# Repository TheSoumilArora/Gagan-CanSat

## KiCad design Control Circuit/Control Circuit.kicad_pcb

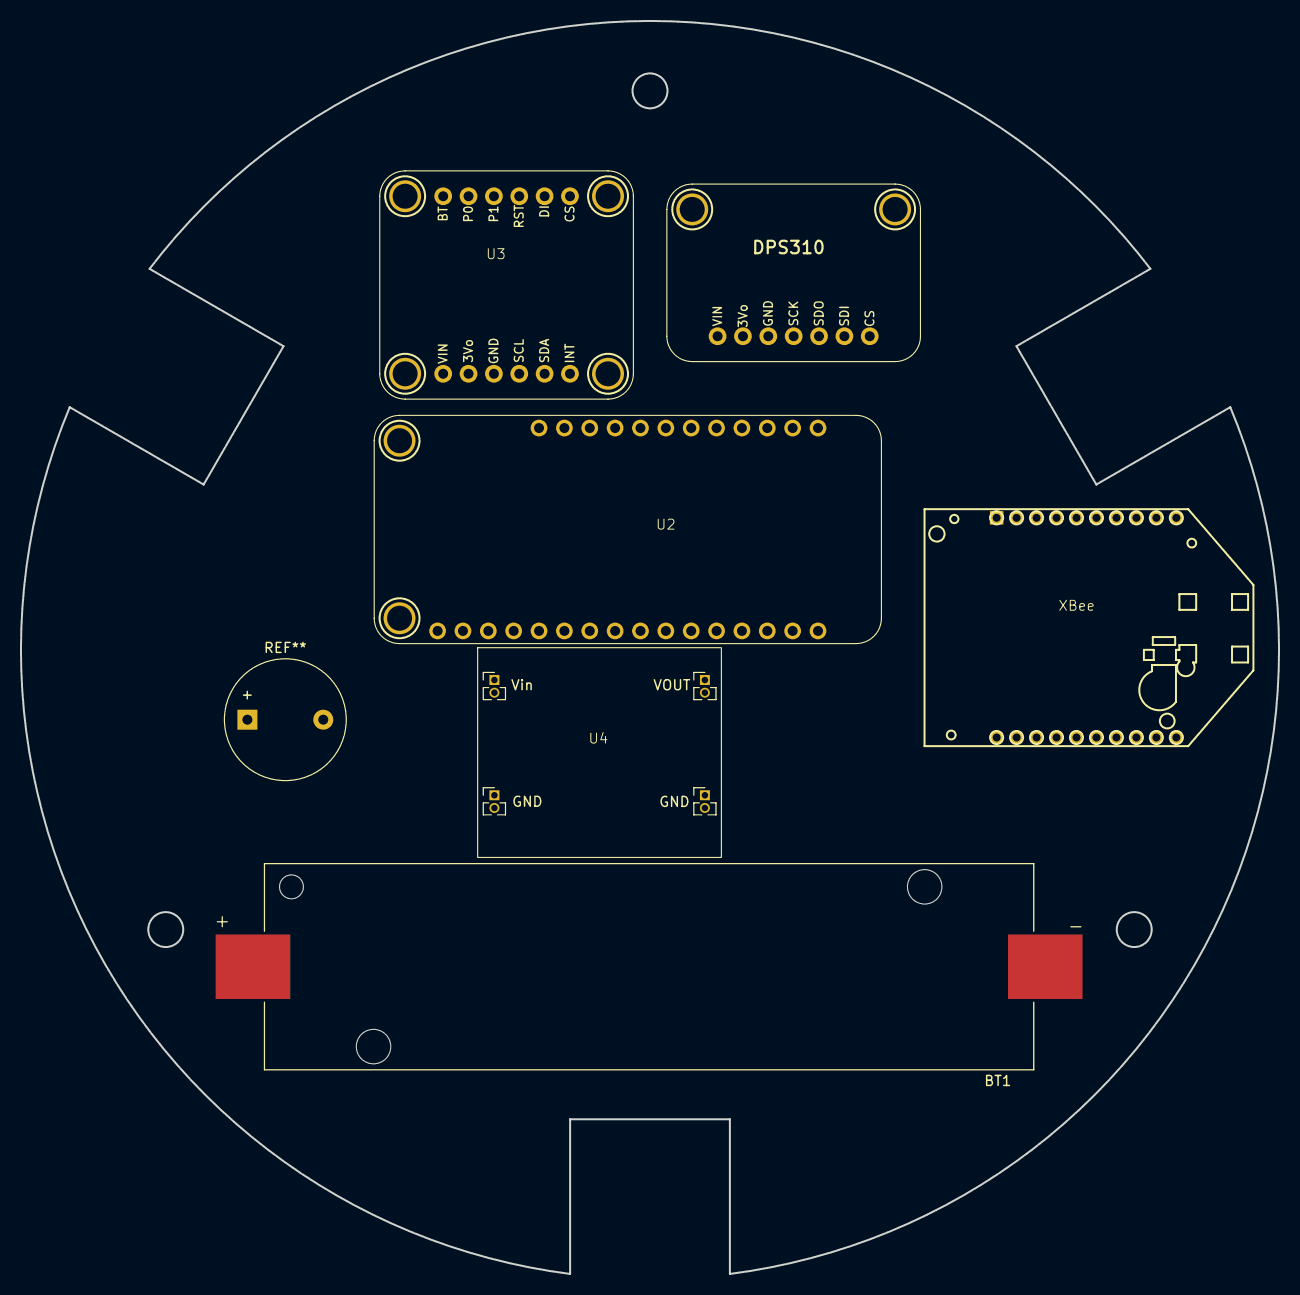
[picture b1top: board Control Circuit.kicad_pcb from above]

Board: 2 copper layers, 126.0 x 125.5 mm, 6 parts (0 on the bottom side), 2 nets, no tracks yet.

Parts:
BT1: 18650 Cell holder; 18560 holder
U1: Adafruit DPS310
U2: Adafruit Feather STM32F405 Express
U3: Adafruit BNO085
U4: TPS61087; TPS61087 Breakout
XBee: Digi XBee

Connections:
unnamed: BT1.N, U4.2 (GND)
unnamed: BT1.P, U4.1 (VIN)

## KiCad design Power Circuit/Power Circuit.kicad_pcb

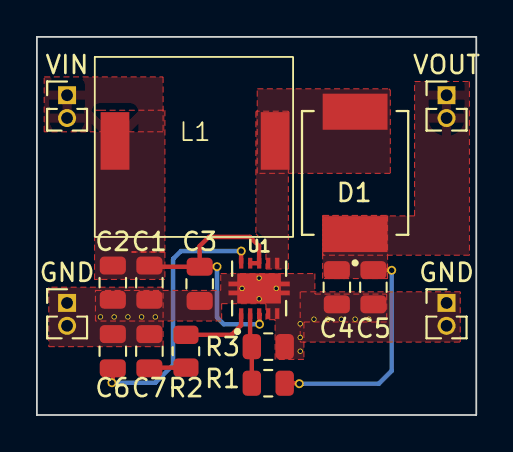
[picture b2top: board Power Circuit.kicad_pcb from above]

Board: 2 copper layers, 24.4 x 21.0 mm, 17 parts (0 on the bottom side), 8 nets.

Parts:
C1, C2, C4, C5: 10uf; C_0805_2012Metric
C3: 1uf; C_0805_2012Metric
C6, C7: 100nf; C_0805_2012Metric
D1: SS34
GND: PinHeader_1x02_P1.27mm_Vertical
GND#2: PinHeader_1x02_P1.27mm_Vertical
L1: 3.3uH; CDRH104R
R1, R2, R3: 18k; R_0805_2012Metric
U1: TPS61087DRCT
VIN: PinHeader_1x02_P1.27mm_Vertical
VOUT: PinHeader_1x02_P1.27mm_Vertical

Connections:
+5V: C4.1, C5.1, D1.C, R3.1, VOUT.1, VOUT.2
GND: C1.2, C2.2, C3.2, C4.2, C5.2, C6.2, C7.2, GND.1, GND.2, GND#2.1, GND#2.2, R1.2, U1.4 (AGND), U1.5 (PGND), U1.11, U1.12, U1.13, U1.14, U1.15
unnamed: C7.1, R2.2
unnamed: R2.1, U1.1 (COMP)
unnamed: R1.1, R3.2, U1.2 (FB)
unnamed: C6.1, U1.10 (SS)
unnamed: D1.A, L1.2, U1.6 (SW), U1.7 (SW-1)
VCC: C1.1, C2.1, C3.1, L1.1, U1.3 (EN), U1.8 (IN), U1.9 (FREQ), VIN.1, VIN.2

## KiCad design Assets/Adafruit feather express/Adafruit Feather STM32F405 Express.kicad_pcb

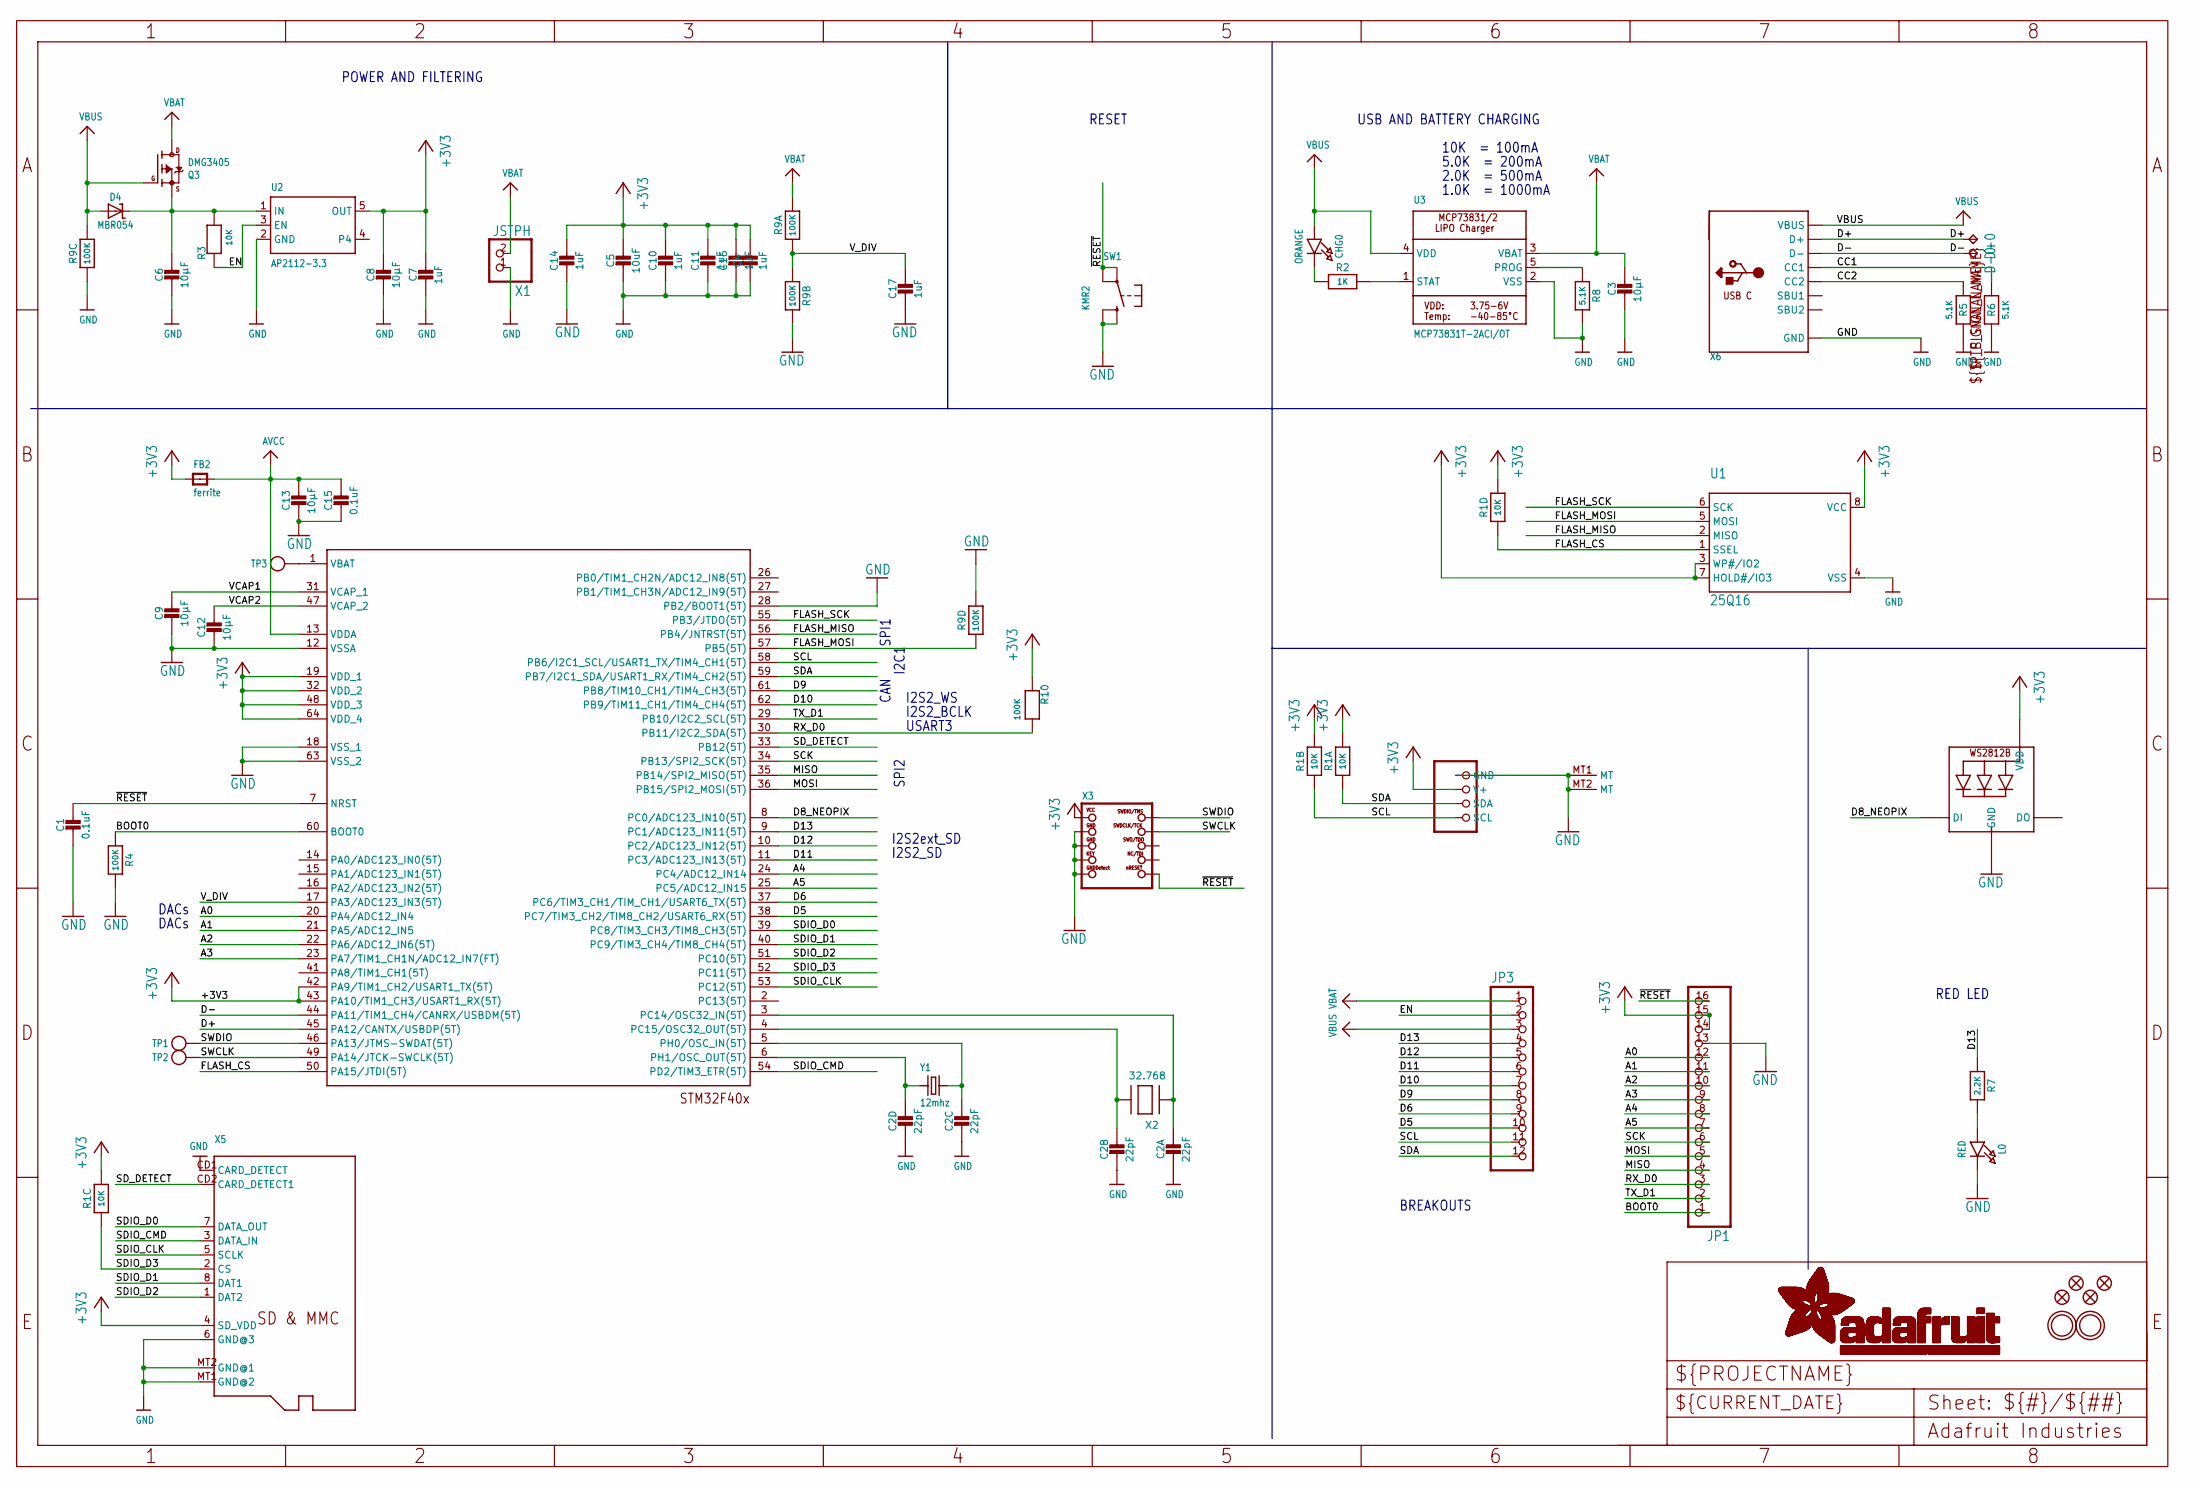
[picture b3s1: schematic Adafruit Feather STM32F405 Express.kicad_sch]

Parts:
C1, C15: 0.1uF; 0603-NO
C2: 22pF; RESPACK_4X0603
C3, C6, C8, C9, C12, C13: 10µF; 0805-NO
C4, C7, C10, C11, C14, C16, C17: 1uF; 0603-NO
C5: 10uF; 0805-NO
CHG0: ORANGE; CHIPLED_0805_NOOUTLINE
CONN1: STEMMA_I2C_QT; JST_SH4
D4: MBR054; SOD-123
D+0: TPB1,27; B1,27
D-0: TPB1,27; B1,27
FB2: ferrite; 0805-NO
JP1: HEADER-1X16ROUND; 1X16_ROUND
JP3: HEADER-1X12; 1X12_ROUND
L0: RED; CHIPLED_0805_NOOUTLINE
LED1: WS2812B3535; LED3535
Q3: DMG3405; SOT23-R
R1: 10K; RESPACK_4X0603_NO
R2: 1K; 0603-NO
R3: 10K; 0603-NO
R4, R10: 100K; 0603-NO
R5, R6, R8: 5.1K; 0603-NO
R7: 2.2K; 0603-NO
R9: 100K; RESPACK_4X0603_NO
SW1: KMR2; BTN_KMR2_4.6X2.8
TP1, TP2, TP3: TESTPOINTROUND1.5MM; TESTPOINT_ROUND_1.5MM
U1: 25Q16; SOIC8_150MIL
U2: AP2112-3.3; SOT23-5
U3: MCP73831T-2ACI/OT; SOT23-5
U$3: STM32F405R; TQFP64
U$5, U$34, U$35, U$37: FIDUCIAL_1MM
U$31, U$32: MOUNTINGHOLE2.5; MOUNTINGHOLE_2.5_PLATED
X1: JSTPH; JSTPH2
X2: 32.768; XTAL3215
X3: JTAG-CORTEX; 2X05_1.27MM_SMT
X5: MICROSD
X6: USB_C; USB_C_CUSB31-CFM2AX-01-X
Y1: 12mhz; CRYSTAL_2.5X2

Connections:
+3V3: C4.1, C5.1, C7.1, C8.1, C10.1, C11.1, C14.1, C16.1, CONN1.2 (V+), FB2.1, JP1.14, JP1.15, LED1.2 (VDD), R1.5 (2), R1.6 (2), R1.7 (2), R1.8 (2), R10.1, U1.3 (WP#/IO2), U1.7 (HOLD#/IO3), U1.8 (VCC), U2.5 (OUT), U$3.19 (VDD_1), U$3.32 (VDD_2), U$3.42 (PA9/TIM1_CH2/USART1_TX(5T)), U$3.43 (PA10/TIM1_CH3/USART1_RX(5T)), U$3.48 (VDD_3), U$3.64 (VDD_4), X3.1 (VCC), X5.4 (SD_VDD)
A0: JP1.12, U$3.20 (PA4/ADC12_IN4)
A1: JP1.11, U$3.21 (PA5/ADC12_IN5)
A2: JP1.10, U$3.22 (PA6/ADC12_IN6(5T))
A3: JP1.9, U$3.23 (PA7/TIM1_CH1N/ADC12_IN7(FT))
A4: JP1.8, U$3.24 (PC4/ADC12_IN14)
A5: JP1.7, U$3.25 (PC5/ADC12_IN15)
AVCC: C13.1, C15.1, FB2.2, U$3.13 (VDDA)
BATTERY: TP3.P$1, U$3.1 (VBAT)
BOOT0: JP1.1, R4.1, U$3.60 (BOOT0)
CC1: R6.2, X6.A5 (CC1)
CC2: R5.2, X6.B5 (CC2)
D5: JP3.10, U$3.38 (PC7/TIM3_CH2/TIM8_CH2/USART6_RX(5T))
D6: JP3.9, U$3.37 (PC6/TIM3_CH1/TIM_CH1/USART6_TX(5T))
D8_NEOPIX: LED1.1 (DI), U$3.8 (PC0/ADC123_IN10(5T))
D9: JP3.8, U$3.61 (PB8/TIM10_CH1/TIM4_CH3(5T))
D10: JP3.7, U$3.62 (PB9/TIM11_CH1/TIM4_CH4(5T))
D11: JP3.6, U$3.11 (PC3/ADC123_IN13(5T))
D12: JP3.5, U$3.10 (PC2/ADC123_IN12(5T))
D13: JP3.4, R7.1, U$3.9 (PC1/ADC123_IN11(5T))
D+: D+0.TP, U$3.45 (PA12/CANTX/USBDP(5T)), X6.A6 (D+), X6.B6 (D+)
D-: D-0.TP, U$3.44 (PA11/TIM1_CH4/CANRX/USBDM(5T)), X6.A7 (D-), X6.B7 (D-)
EN: JP3.2, R3.1, U2.3 (EN)
FLASH_CS: R1.4 (1), U1.1 (SSEL), U$3.50 (PA15/JTDI(5T))
FLASH_MISO: U1.2 (MISO), U$3.56 (PB4/JNTRST(5T))
FLASH_MOSI: R9.4 (1), U1.5 (MOSI), U$3.57 (PB5(5T))
FLASH_SCK: U1.6 (SCK), U$3.55 (PB3/JTDO(5T))
GND: C1.2, C2.5 (2), C2.6 (2), C2.7 (2), C2.8 (2), C3.2, C4.2, C5.2, C6.2, C7.2, C8.2, C9.2, C10.2, C11.2, C12.2, C13.2, C14.2, C15.2, C16.2, C17.2, CONN1.1 (GND), CONN1.MT1 (MT), CONN1.MT2 (MT), JP1.13, L0.C, LED1.4 (GND), R4.2, R5.1, R6.1, R8.2, R9.3 (1), R9.5 (2), R9.7 (2), SW1.B (S), SW1.B' (S1), U1.4 (VSS), U2.2 (GND), U3.2 (VSS), U$3.12 (VSSA), U$3.18 (VSS_1), U$3.28 (PB2/BOOT1(5T)), U$3.63 (VSS_2), X1.1, X3.3 (GND@1), X3.5 (GND@2), X3.7 (KEY), X3.9 (GNDDETECT), X5.6 (GND@3), X5.CD1 (CARD_DETECT), X5.MT1 (GND@2), X5.MT2 (GND@1), X6.A1B12 (GND), X6.B1A12 (GND)
MISO: JP1.4, U$3.35 (PB14/SPI2_MISO(5T))
MOSI: JP1.5, U$3.36 (PB15/SPI2_MOSI(5T))
unnamed: CHG0.C, R2.1
unnamed: L0.A, R7.2
unnamed: R2.2, U3.1 (STAT)
unnamed: R8.1, U3.5 (PROG)
unnamed: C2.4 (1), U$3.3 (PC14/OSC32_IN(5T)), X2.P$1
unnamed: C2.2 (1), U$3.5 (PH0/OSC_IN(5T)), Y1.3 (2)
unnamed: C2.3 (1), U$3.4 (PC15/OSC32_OUT(5T)), X2.P$2
unnamed: C2.1, U$3.6 (PH1/OSC_OUT(5T)), Y1.1
RX_D0: JP1.3, R10.2, U$3.30 (PB11/I2C2_SDA(5T))
SCK: JP1.6, U$3.34 (PB13/SPI2_SCK(5T))
SCL: CONN1.4 (SCL), JP3.11, R1.2 (1), U$3.58 (PB6/I2C1_SCL/USART1_TX/TIM4_CH1(5T))
SDA: CONN1.3 (SDA), JP3.12, R1.1, U$3.59 (PB7/I2C1_SDA/USART1_RX/TIM4_CH2(5T))
SDIO_CLK: U$3.53 (PC12(5T)), X5.5 (SCLK)
SDIO_CMD: U$3.54 (PD2/TIM3_ETR(5T)), X5.3 (DATA_IN)
SDIO_D0: U$3.39 (PC8/TIM3_CH3/TIM8_CH3(5T)), X5.7 (DATA_OUT)
SDIO_D1: U$3.40 (PC9/TIM3_CH4/TIM8_CH4(5T)), X5.8 (DAT1)
SDIO_D2: U$3.51 (PC10(5T)), X5.1 (DAT2)
SDIO_D3: R1.3 (1), U$3.52 (PC11(5T)), X5.2 (CS)
SD_DETECT: U$3.33 (PB12(5T)), X5.CD2 (CARD_DETECT1)
SWCLK: TP2.P$1, U$3.49 (PA14/JTCK-SWCLK(5T)), X3.4 (SWDCLK)
SWDIO: TP1.P$1, U$3.46 (PA13/JTMS-SWDAT(5T)), X3.2 (SWDIO)
TX_D1: JP1.2, U$3.29 (PB10/I2C2_SCL(5T))
VBAT: C3.1, JP3.1, Q3.3 (D), R9.8 (2), U3.3 (VBAT), X1.2
VBUS: CHG0.A, D4.A, JP3.3, Q3.1 (G), R9.6 (2), U3.4 (VDD), X6.A4B9 (VBUS), X6.B4A9 (VBUS)
VCAP1: C9.1, U$3.31 (VCAP_1)
VCAP2: C12.1, U$3.47 (VCAP_2)
VHI: C6.1, D4.C, Q3.2 (S), R3.2, U2.1 (IN)
V_DIV: C17.1, R9.1, R9.2 (1), U$3.17 (PA3/ADC123_IN3(5T))
~RESET: C1.1, JP1.16, SW1.A, SW1.A' (P1), U$3.7 (NRST), X3.10 (NRESET)

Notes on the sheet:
SPI1
RED LED
RESET
I2S2_BCLK
2.0K = 500mA
I2S2_SD
5.0K = 200mA
USART3
1.0K = 1000mA
USB AND BATTERY CHARGING
DACs
I2S2ext_SD
I2C1
I2S2_WS
10K = 100mA
POWER AND FILTERING
CAN
SPI2
BREAKOUTS

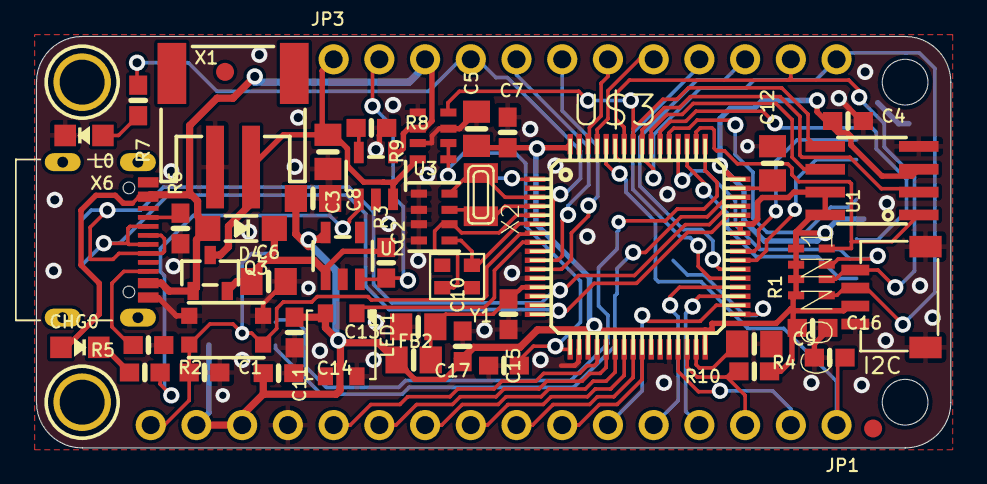
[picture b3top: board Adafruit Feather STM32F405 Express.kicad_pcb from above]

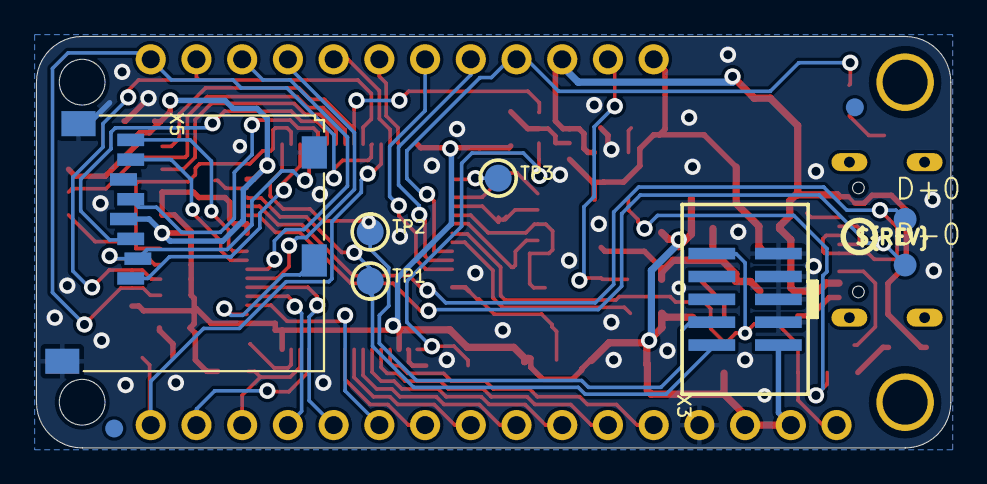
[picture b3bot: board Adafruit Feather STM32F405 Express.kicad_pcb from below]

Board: 2 copper layers, 50.8 x 22.9 mm, 63 parts (11 on the bottom side), 59 nets.

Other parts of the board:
@HOLE0, @HOLE1: (no value)
U$13: PCBFEAT-REV-040
U$24: FEATHER_STM32F405_TOP
U$40: FEATHER_STM32F405_BOT

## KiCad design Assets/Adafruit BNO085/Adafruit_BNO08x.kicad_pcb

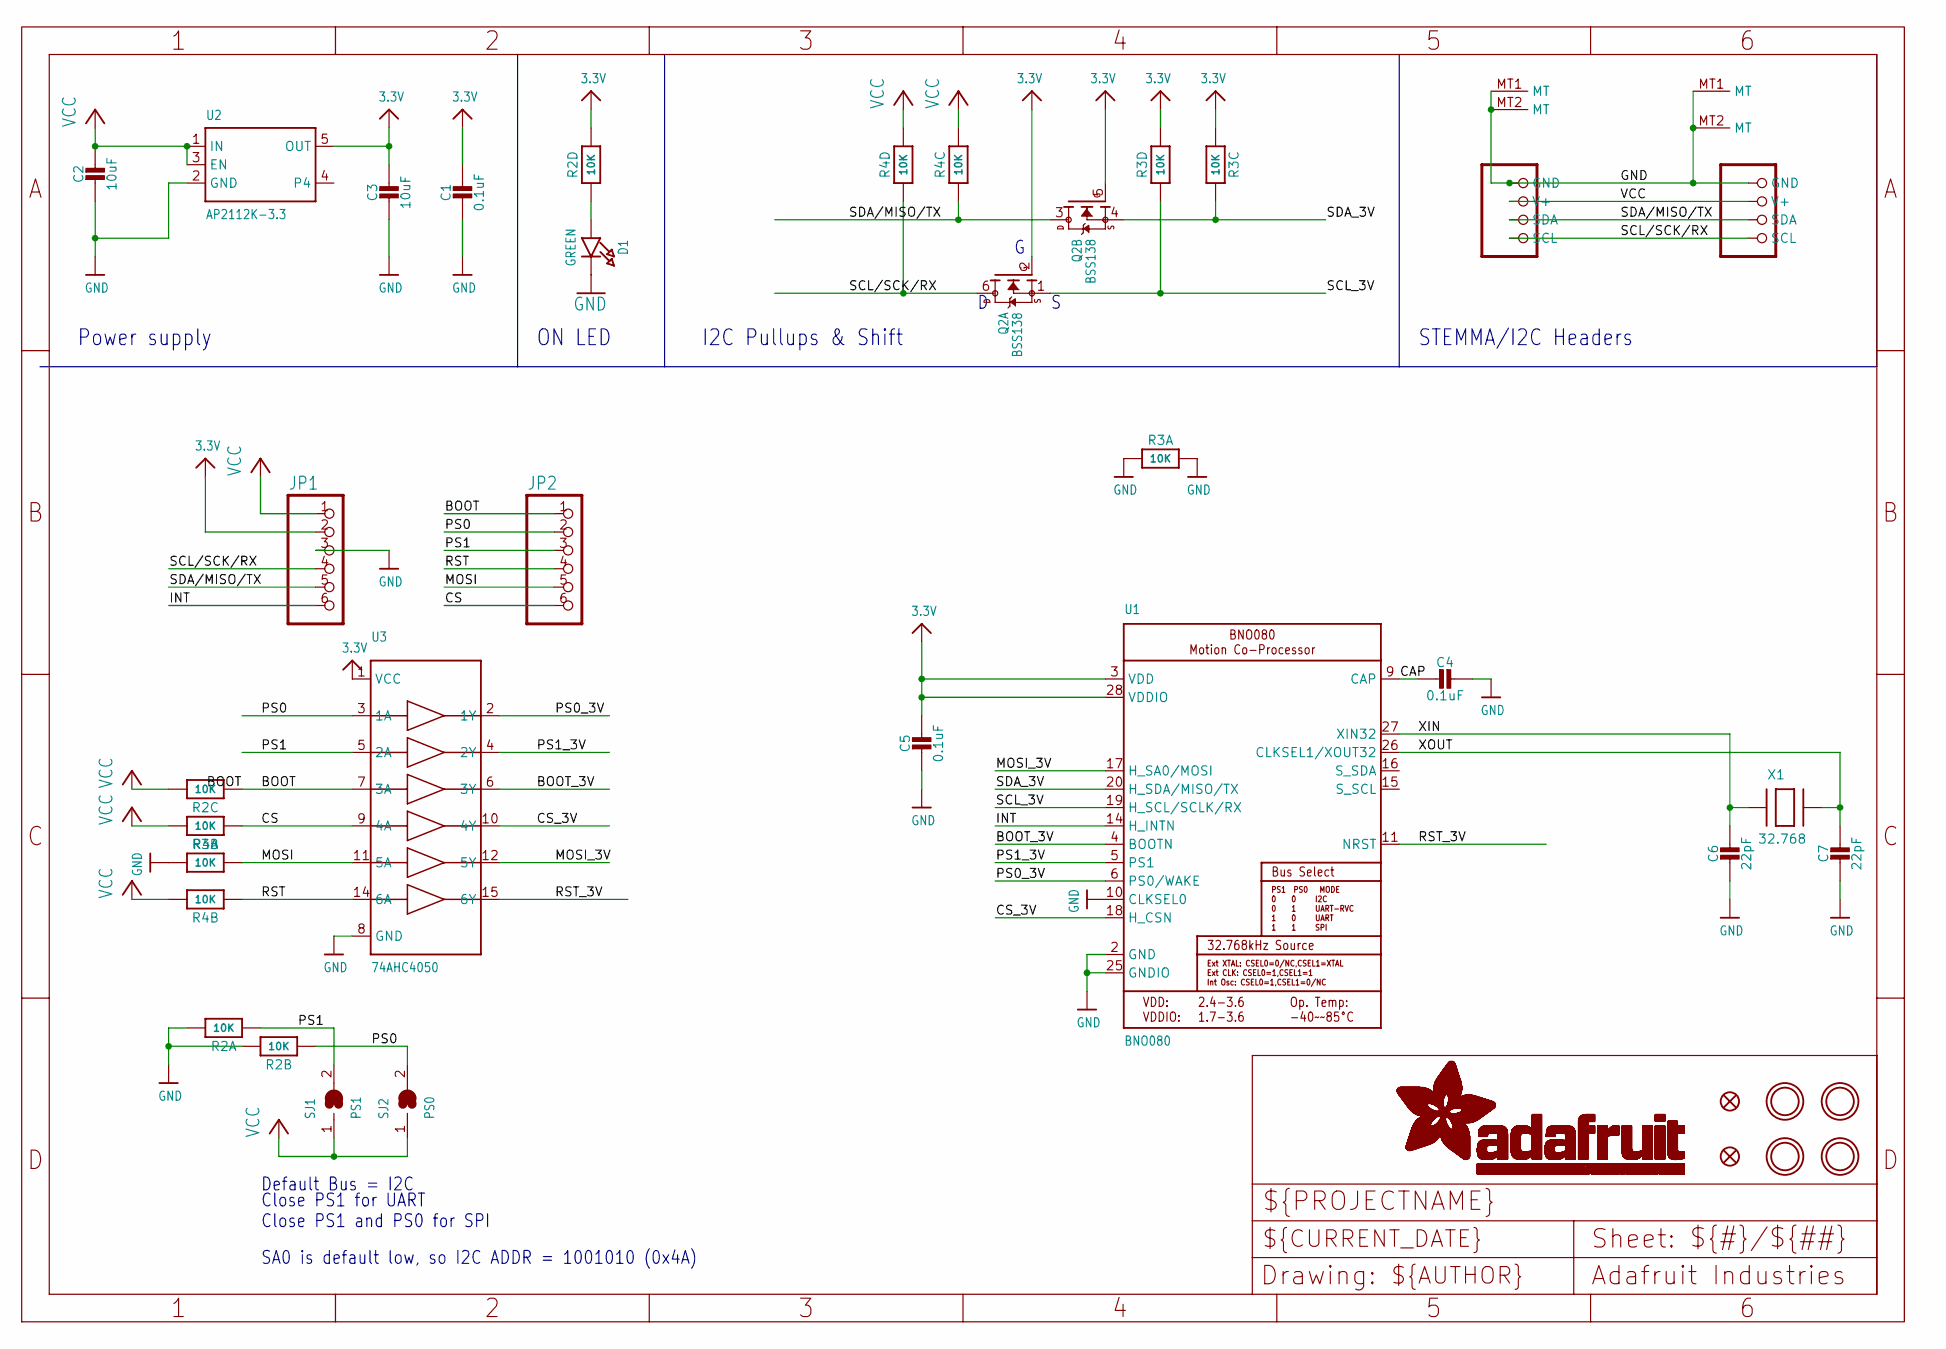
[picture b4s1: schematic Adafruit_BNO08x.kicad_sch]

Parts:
C1, C4, C5: 0.1uF; 0603-NO
C2, C3: 10uF; 0805-NO
C6, C7: 22pF; 0603-NO
CONN3, CONN4: STEMMA_I2C_QT; JST_SH4
D1: GREEN; CHIPLED_0603_NOOUTLINE
FID3, FID4: FIDUCIAL_1MM
JP1, JP2: HEADER-1X670MIL; 1X06_ROUND_70
Q2: BSS138; SOT363
R2, R3, R4: 10K; RESPACK_4X0603
SJ1: PS1; SOLDERJUMPER_ARROW_NOPASTE
SJ2: PS0; SOLDERJUMPER_ARROW_NOPASTE
U1: BNO080
U2: AP2112K-3.3; SOT23-5
U3: 74AHC4050; TSSOP16
U$1, U$17, U$19, U$21: MOUNTINGHOLE2.5; MOUNTINGHOLE_2.5_PLATED
X1: 32.768; XTAL3215

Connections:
3.3V: C1.1, C3.1, C5.1, JP1.2, Q2.2 (G), Q2.5 (G), R2.5 (2), R3.3 (1), R3.5 (2), U1.3 (VDD), U1.28 (VDDIO), U2.5 (OUT), U3.1 (VCC)
BOOT: JP2.1, R2.3 (1), U3.7 (3A)
BOOT_3V: U1.4 (BOOTN), U3.6 (3Y)
CAP: C4.2, U1.9 (CAP)
CS: JP2.6, R4.1, U3.9 (4A)
CS_3V: U1.18 (H_CSN), U3.10 (4Y)
GND: C1.2, C2.2, C3.2, C4.1, C5.2, C6.2, C7.2, CONN3.1 (GND), CONN3.MT1 (MT), CONN3.MT2 (MT), CONN4.1 (GND), CONN4.MT1 (MT), CONN4.MT2 (MT), D1.C, JP1.3, R2.7 (2), R2.8 (2), R3.1, R3.2 (1), R3.8 (2), U1.2 (GND), U1.10 (CLKSEL0), U1.25 (GNDIO), U2.2 (GND), U3.8 (GND)
INT: JP1.6, U1.14 (H_INTN)
MOSI: JP2.5, R3.7 (2), U3.11 (5A)
MOSI_3V: U1.17 (H_SA0/MOSI), U3.12 (5Y)
unnamed: D1.A, R2.4 (1)
PS0: JP2.2, R2.2 (1), SJ2.2, U3.3 (1A)
PS0_3V: U1.6 (PS0/WAKE), U3.2 (1Y)
PS1: JP2.3, R2.1, SJ1.2, U3.5 (2A)
PS1_3V: U1.5 (PS1), U3.4 (2Y)
RST: JP2.4, R4.2 (1), U3.14 (6A)
RST_3V: U1.11 (NRST), U3.15 (6Y)
SCL/SCK/RX: CONN3.4 (SCL), CONN4.4 (SCL), JP1.4, Q2.6 (D), R4.4 (1)
SCL_3V: Q2.1 (S), R3.4 (1), U1.19 (H_SCL/SCLK/RX)
SDA/MISO/TX: CONN3.3 (SDA), CONN4.3 (SDA), JP1.5, Q2.3 (D), R4.3 (1)
SDA_3V: Q2.4 (S), R3.6 (2), U1.20 (H_SDA/MISO/TX)
VCC: C2.1, CONN3.2 (V+), CONN4.2 (V+), JP1.1, R2.6 (2), R4.5 (2), R4.6 (2), R4.7 (2), R4.8 (2), SJ1.1, SJ2.1, U2.1 (IN), U2.3 (EN)
XIN: C6.1, U1.27 (XIN32), X1.P$1
XOUT: C7.1, U1.26 (CLKSEL1/XOUT32), X1.P$2

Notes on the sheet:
SA0 is default low, so I2C ADDR = 1001010 (0x4A)
Close PS1 for UART Close PS1 and PS0 for SPI
Power supply
STEMMA/I2C Headers
I2C Pullups & Shift
Default Bus = I2C
ON LED

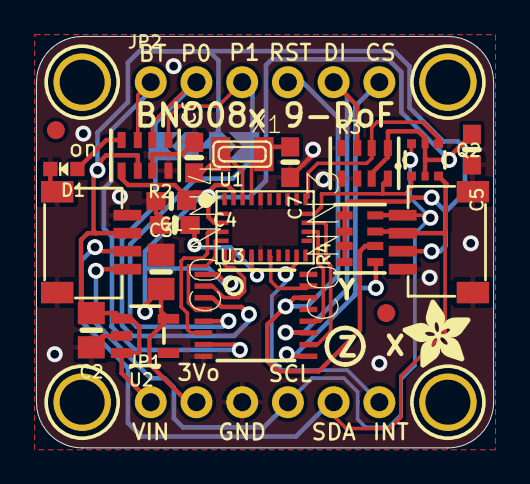
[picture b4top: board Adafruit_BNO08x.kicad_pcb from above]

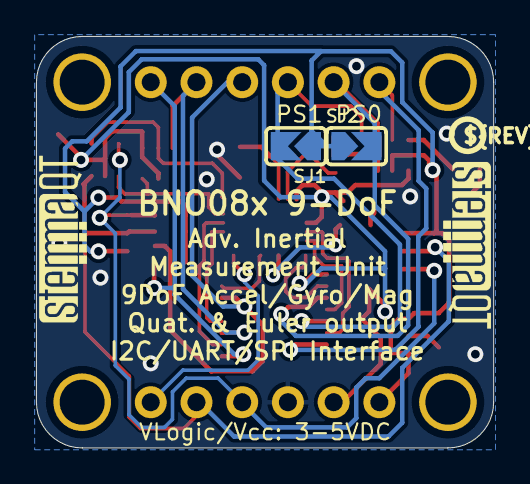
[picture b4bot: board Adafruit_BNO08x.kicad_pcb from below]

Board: 2 copper layers, 25.4 x 22.9 mm, 32 parts (5 on the bottom side), 24 nets.

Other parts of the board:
U$22: ADAFRUIT_3.5MM
U$25: PCBFEAT-REV-040
U$30, U$31: STEMMAQT

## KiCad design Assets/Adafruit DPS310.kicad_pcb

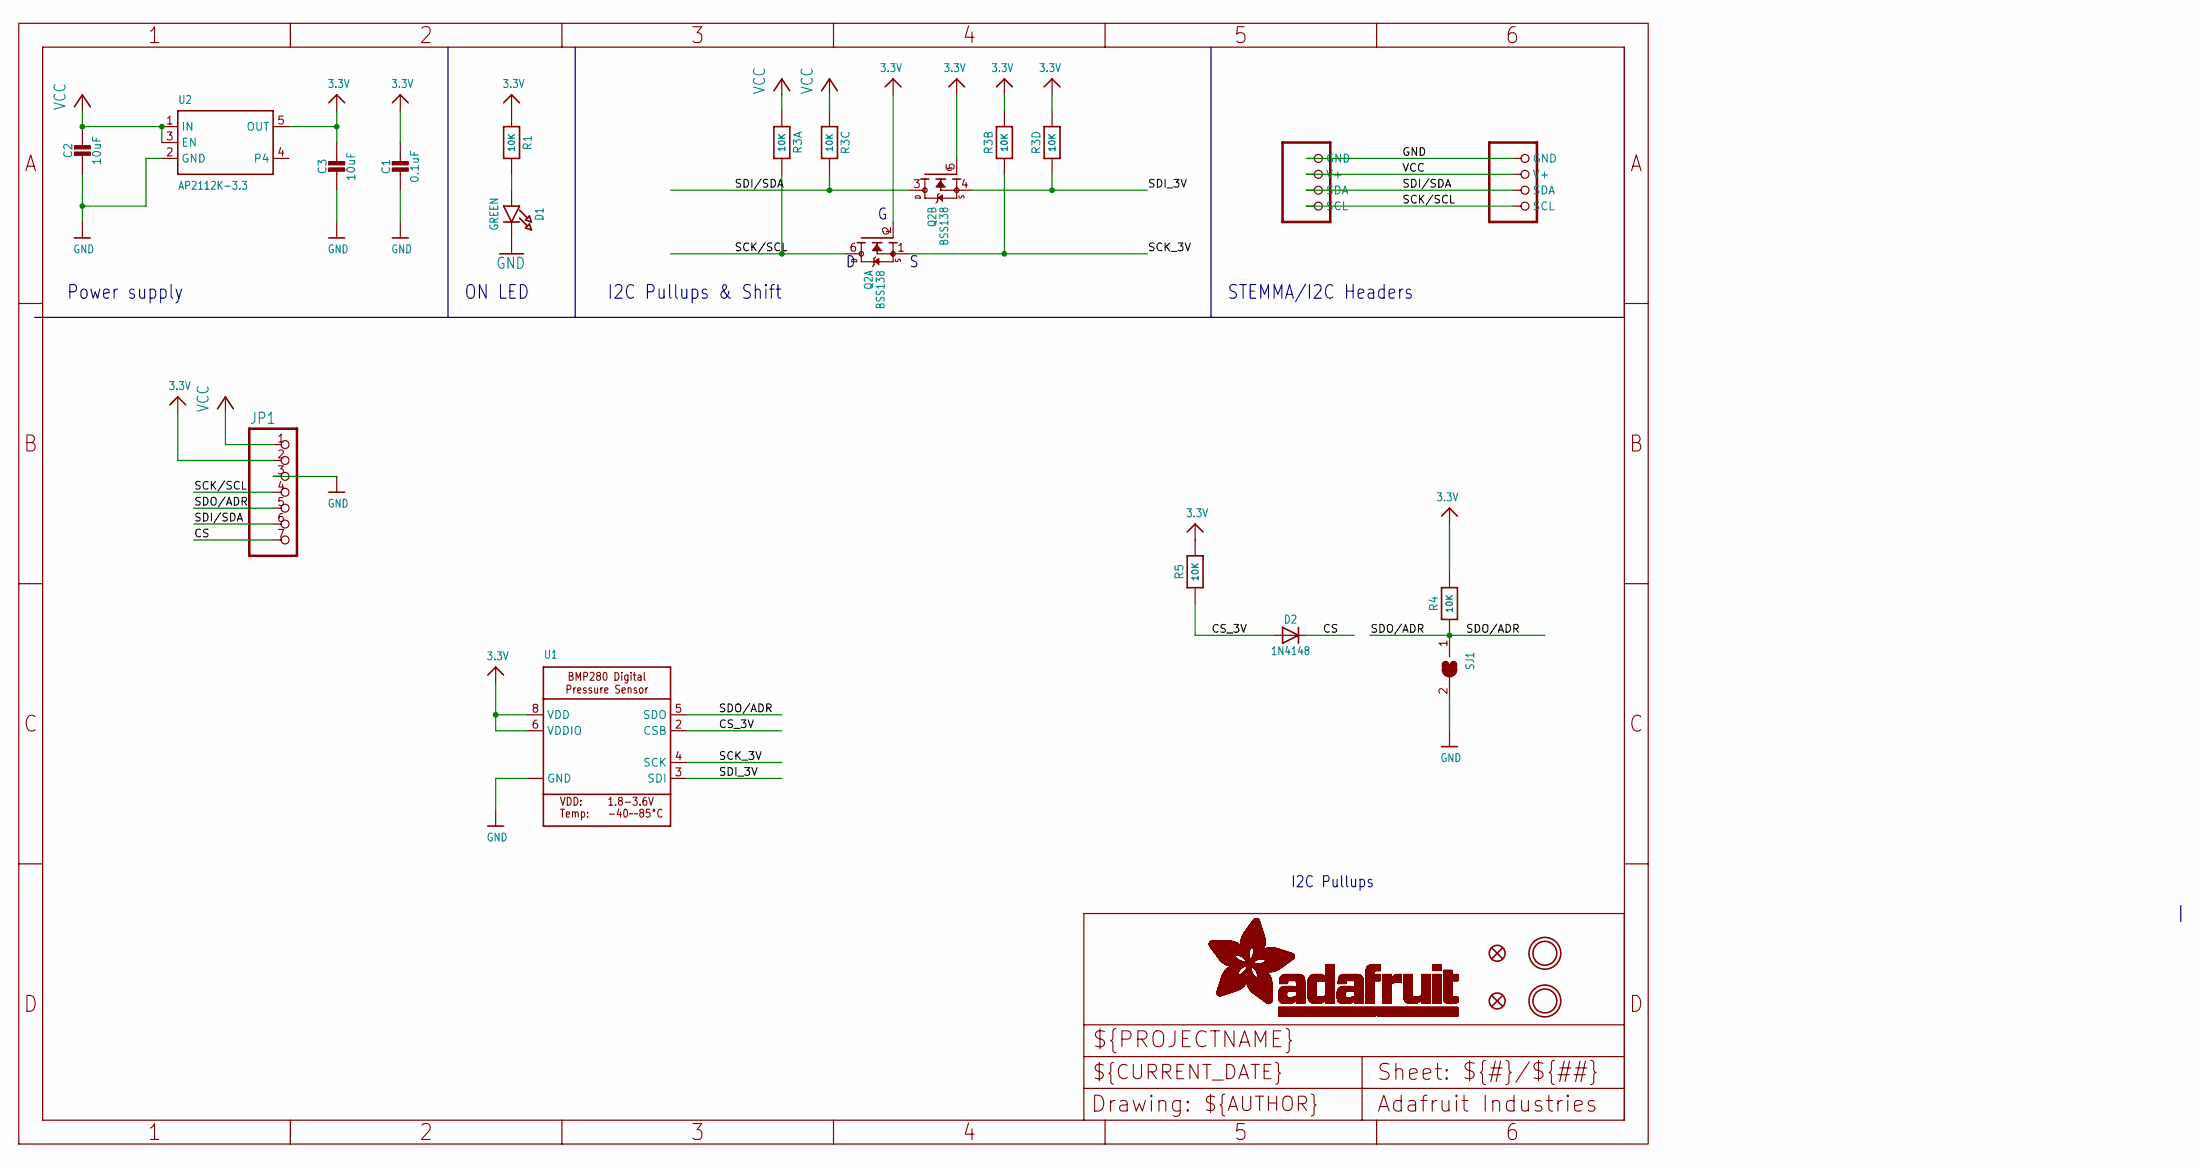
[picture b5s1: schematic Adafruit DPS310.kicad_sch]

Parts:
C1: 0.1uF; 0603-NO
C2, C3: 10uF; 0805-NO
CONN3, CONN4: STEMMA_I2C_QT; JST_SH4
D1: GREEN; CHIPLED_0603_NOOUTLINE
D2: 1N4148; SOD-323
FID3, FID4: FIDUCIAL_1MM
JP1: HEADER-1X770MIL; 1X07_ROUND_70
Q2: BSS138; SOT363
R1, R4, R5: 10K; 0603-NO
R3: 10K; RESPACK_4X0603
SJ1: SOLDERJUMPER; SOLDERJUMPER_ARROW_NOPASTE
U1: BMP280_COMBO; BMX280_COMBO
U2: AP2112K-3.3; SOT23-5
U$1, U$17: MOUNTINGHOLE2.5; MOUNTINGHOLE_2.5_PLATED

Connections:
3.3V: C1.1, C3.1, JP1.2, Q2.2 (G), Q2.5 (G), R1.1, R3.2 (1), R3.4 (1), R4.2, R5.2, U1.6 (VDDIO), U1.8 (VDD), U2.5 (OUT)
CS: D2.C, JP1.7
CS_3V: D2.A, R5.1, U1.2 (CSB)
GND: C1.2, C2.2, C3.2, CONN3.1 (GND), CONN4.1 (GND), D1.C, JP1.3, SJ1.2, U1.1 (GND), U1.7 (GND), U2.2 (GND)
unnamed: D1.A, R1.2
SCK/SCL: CONN3.4 (SCL), CONN4.4 (SCL), JP1.4, Q2.6 (D), R3.8 (2)
SCK_3V: Q2.1 (S), R3.7 (2), U1.4 (SCK)
SDI/SDA: CONN3.3 (SDA), CONN4.3 (SDA), JP1.6, Q2.3 (D), R3.6 (2)
SDI_3V: Q2.4 (S), R3.5 (2), U1.3 (SDI)
SDO/ADR: JP1.5, R4.1, SJ1.1, U1.5 (SDO)
VCC: C2.1, CONN3.2 (V+), CONN4.2 (V+), JP1.1, R3.1, R3.3 (1), U2.1 (IN), U2.3 (EN)

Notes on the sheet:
ON LED
I2C Pullups & Shift
STEMMA/I2C Headers
I2C Pullups
Power supply

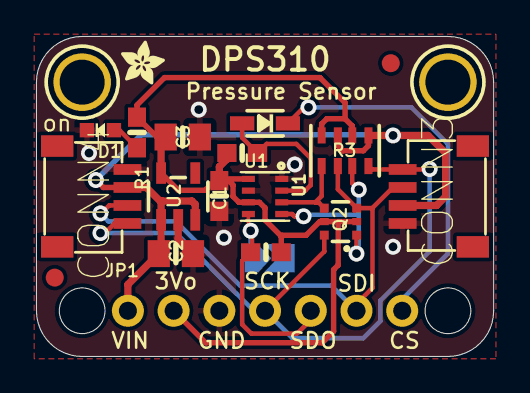
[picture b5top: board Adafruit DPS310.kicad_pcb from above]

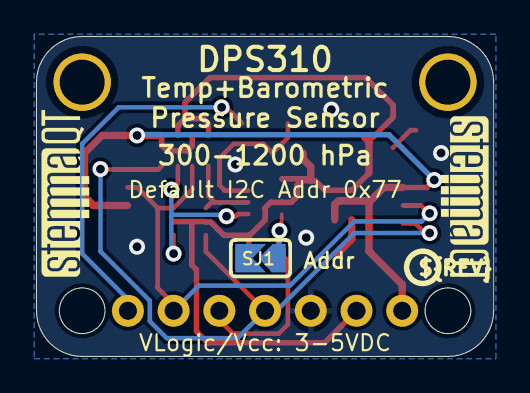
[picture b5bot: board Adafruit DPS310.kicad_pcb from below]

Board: 2 copper layers, 25.4 x 17.8 mm, 26 parts (4 on the bottom side), 11 nets.

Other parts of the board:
@HOLE0, @HOLE1: (no value)
U$4: ADAFRUIT_2.5MM
U$25: PCBFEAT-REV-040
U$30, U$31: STEMMAQT

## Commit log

2024-01-18 Added Flight Software basic Structure
2024-01-18 added files for Circuit design
2024-01-18 added lisence
2024-01-23 Updated .dxf and control circuit PCB with 3mm tolerance
2024-01-24 added Baro PCB Files
2024-01-24 PCB for IMU added
2024-01-24 Added symbol and footprint for baro and IMU
2024-01-24 removed backup files
2024-01-25 added stm32d411 files
2024-01-25 added stm step file
2024-01-25 added symbol for sensors
2024-01-26 added stm32f405 board files
2024-01-26 fixed .step file not loading
2024-01-26 fixed board outline and added mounting holes
2024-01-27 added power conversion pcb
2024-01-27 added boost converter
2024-01-29 added symbol and foot print for boost converter
2024-01-29 using lfs
